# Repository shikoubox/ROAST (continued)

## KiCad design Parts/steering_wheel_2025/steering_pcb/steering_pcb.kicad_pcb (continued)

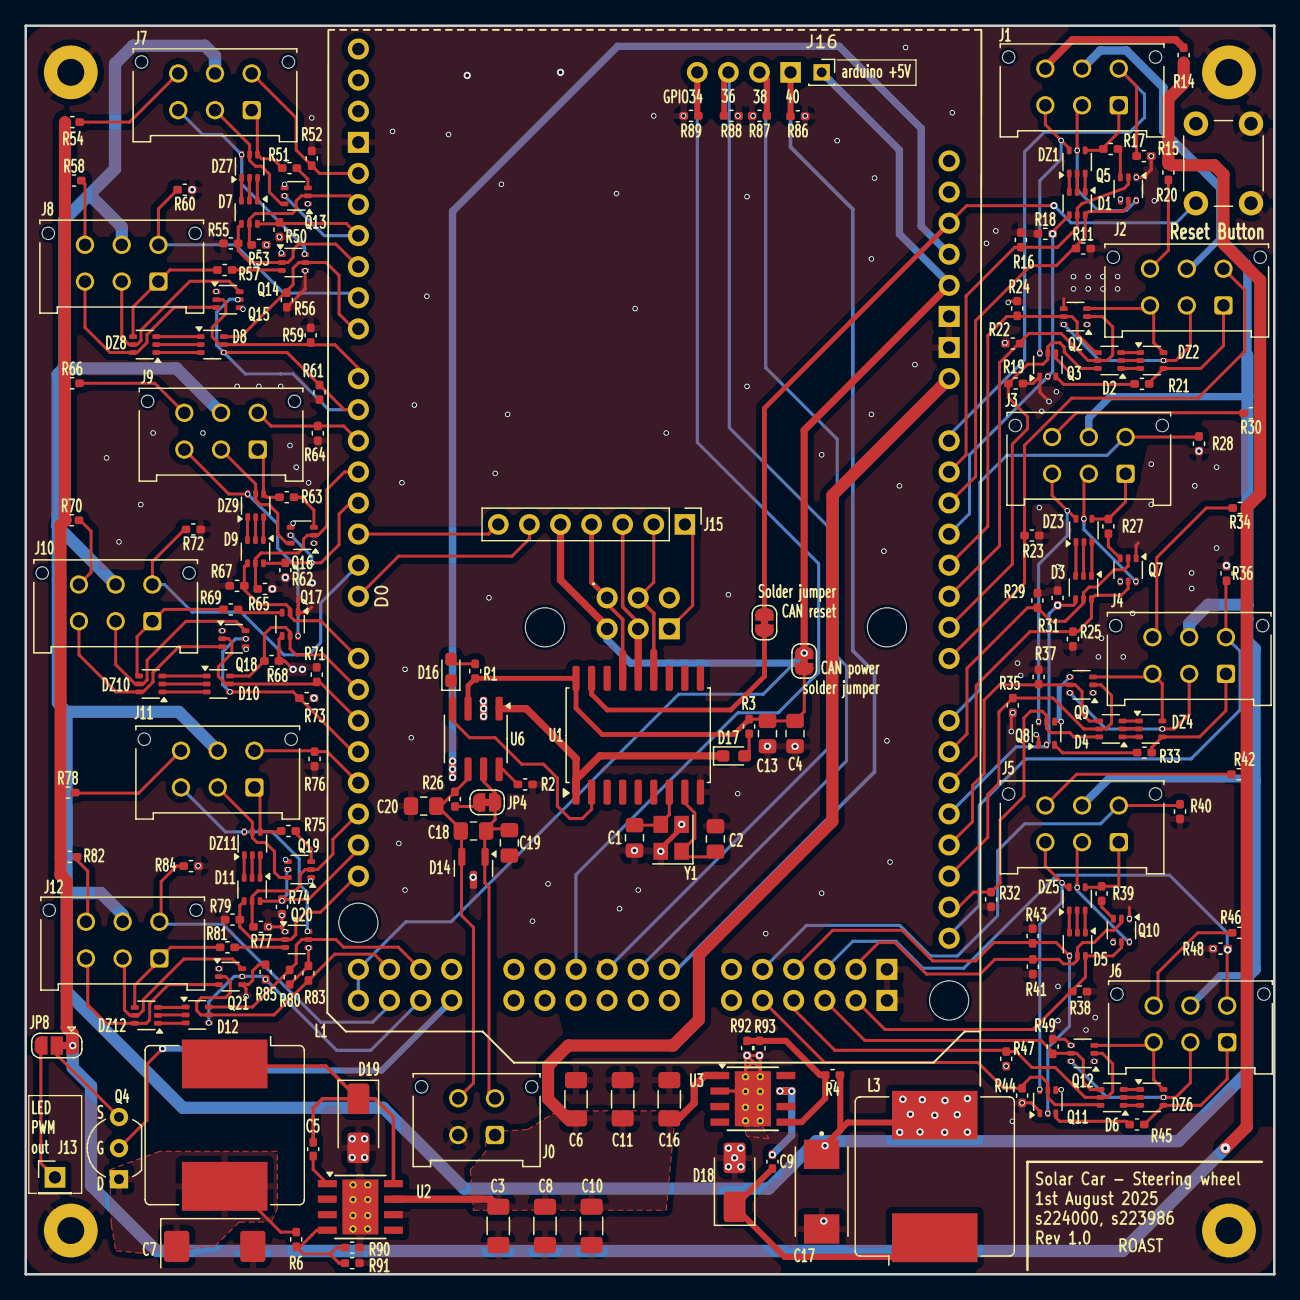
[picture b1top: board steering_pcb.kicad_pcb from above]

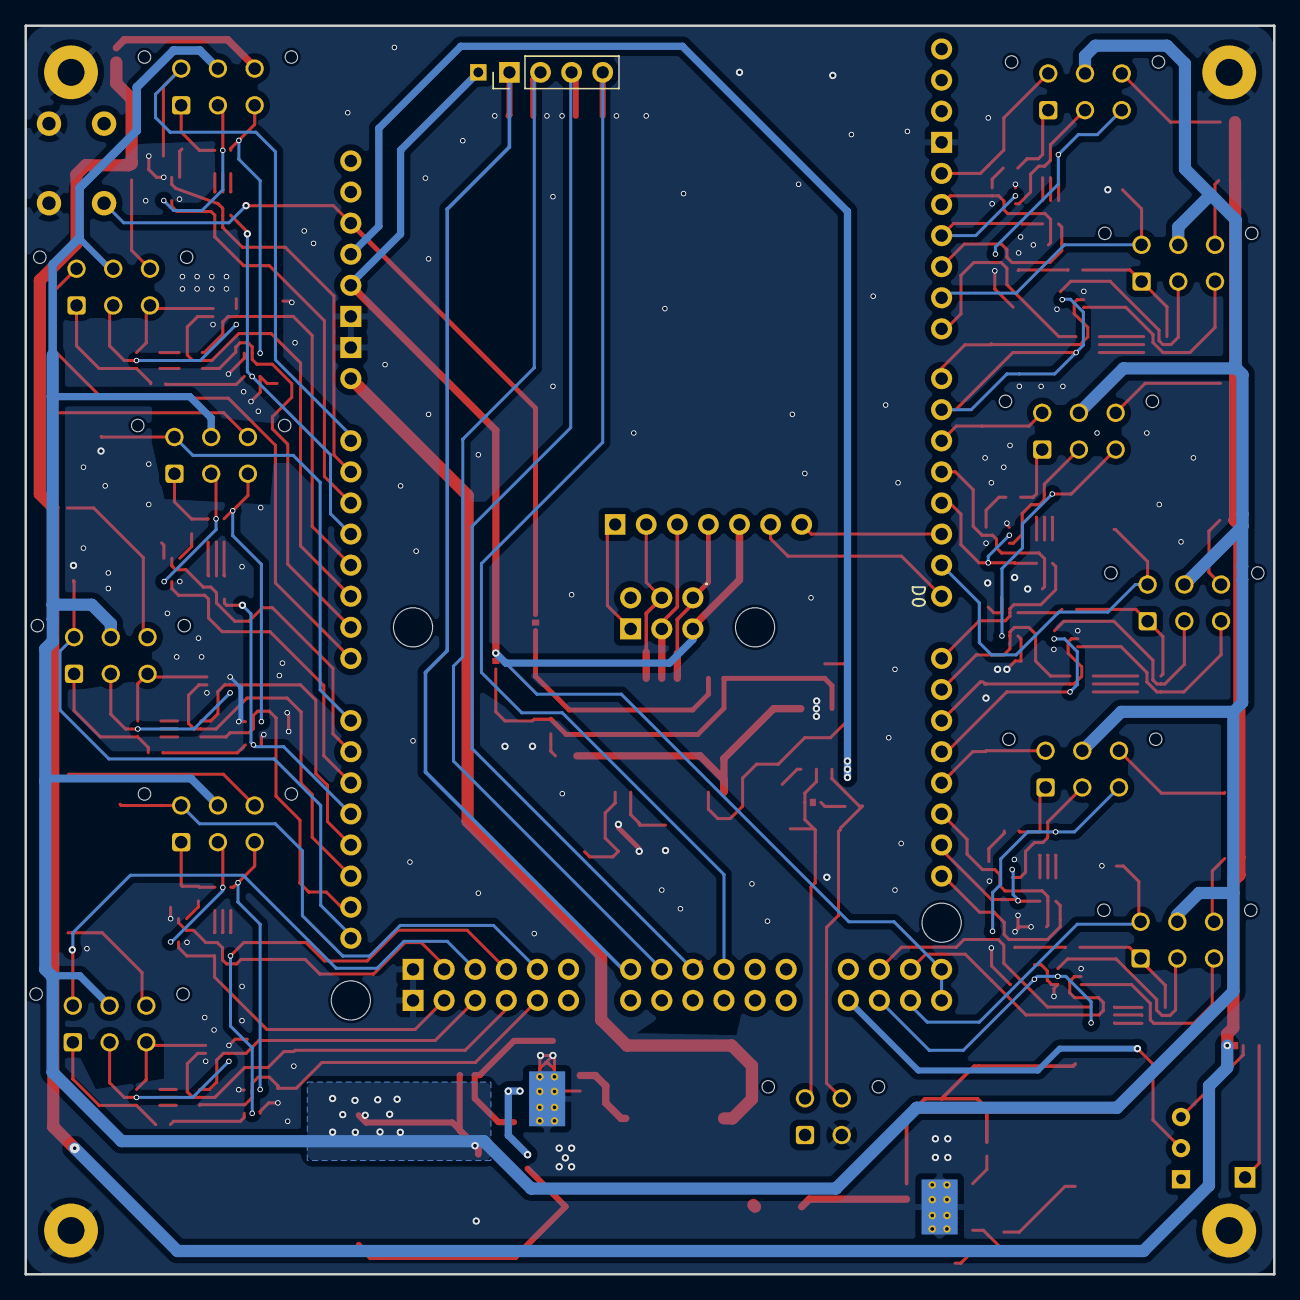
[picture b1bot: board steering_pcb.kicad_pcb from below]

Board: 2 copper layers, 102.0 x 102.0 mm, 185 parts (2 on the bottom side), 183 nets.

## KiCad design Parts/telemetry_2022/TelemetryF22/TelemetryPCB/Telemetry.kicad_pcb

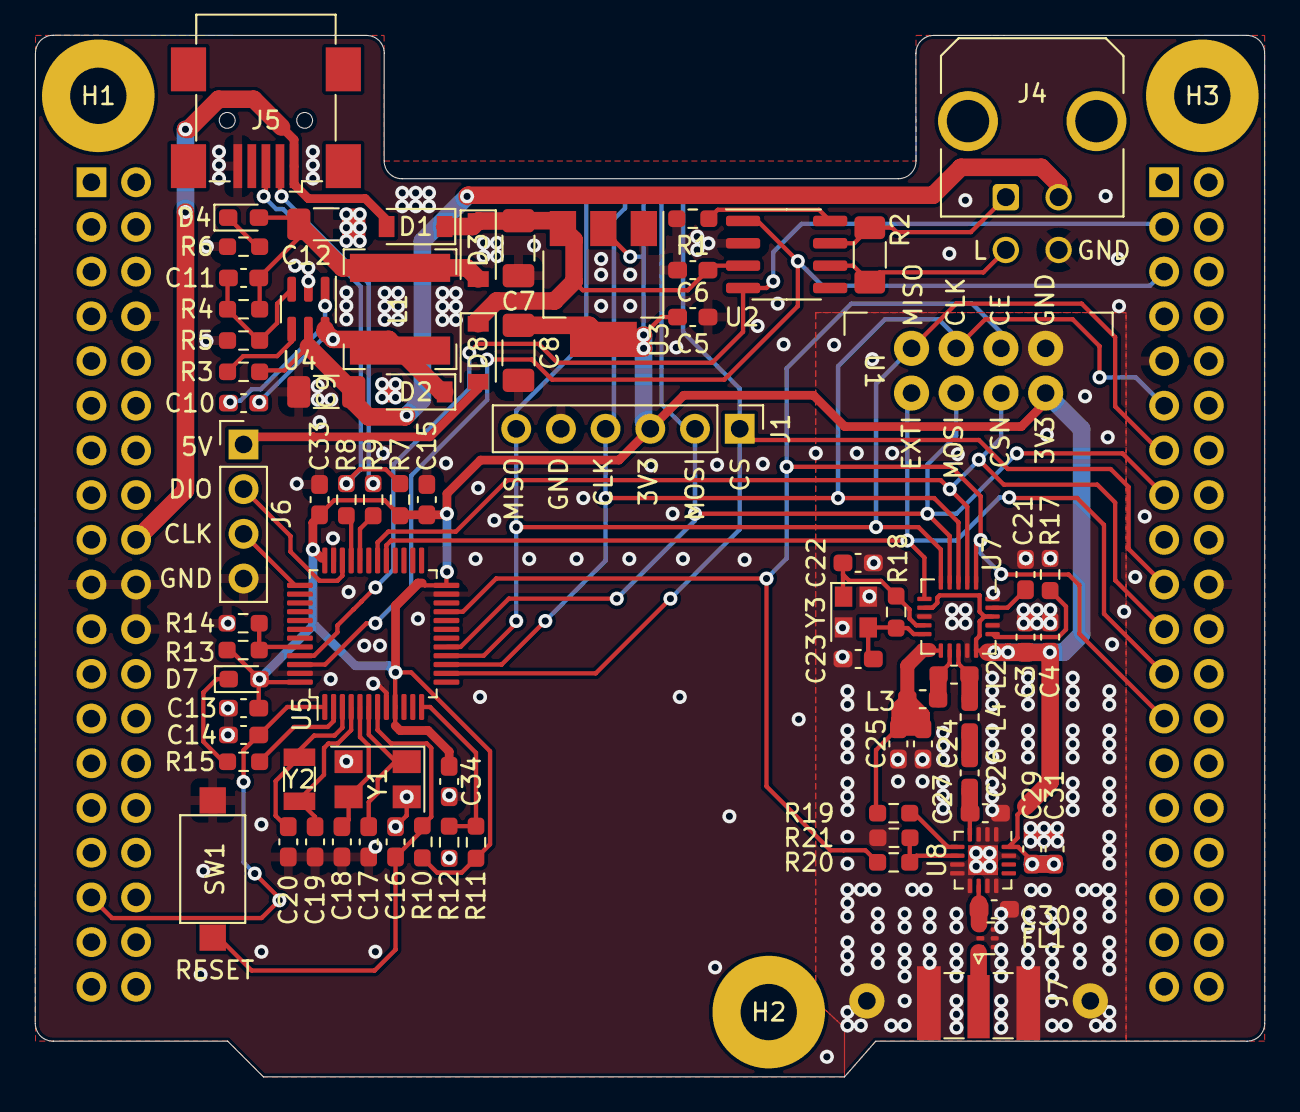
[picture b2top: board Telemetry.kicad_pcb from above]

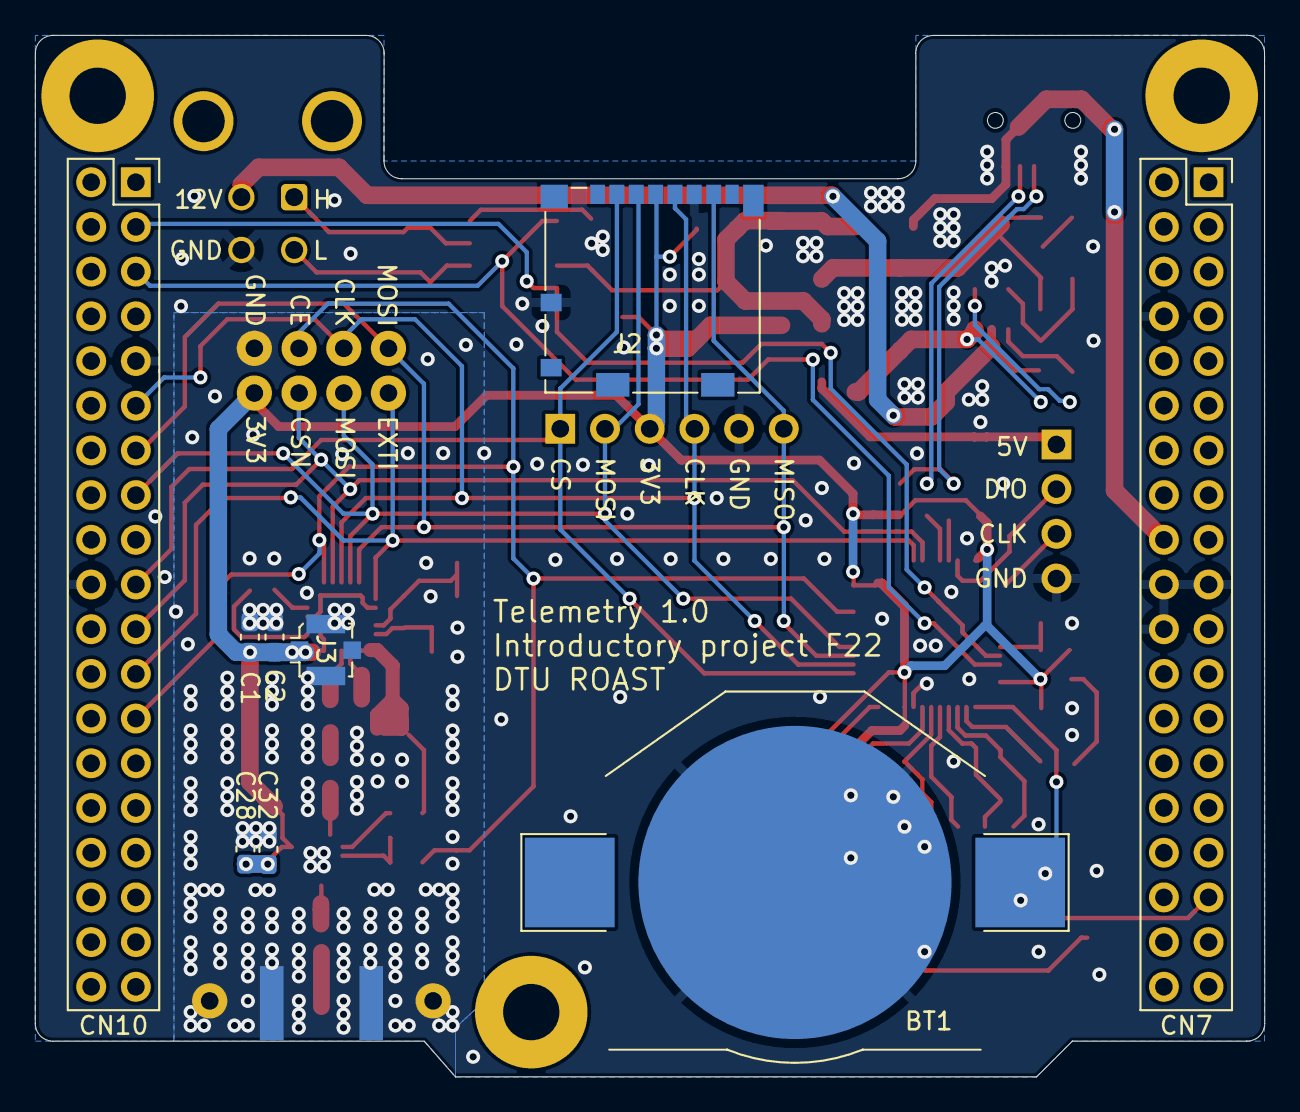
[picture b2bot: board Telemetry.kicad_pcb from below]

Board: 2 copper layers, 69.9 x 59.2 mm, 89 parts (9 on the bottom side), 53 nets.

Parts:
BT1: Battery_Cell; BatteryHolder_Keystone_3002_1x2032
C1, C13, C28: 1u; C_0603_1608Metric_Pad1.08x0.95mm_HandSolder
C2, C32: 100p; C_0603_1608Metric_Pad1.08x0.95mm_HandSolder
C3, C31: 10n; C_0603_1608Metric_Pad1.08x0.95mm_HandSolder
C4, C5, C6, C14, C15, C29, C33, C34: 100n; C_0603_1608Metric_Pad1.08x0.95mm_HandSolder
C7, C8, C9, C12: 10u; C_1206_3216Metric_Pad1.33x1.80mm_HandSolder
C10, C16: 22n; C_0603_1608Metric_Pad1.08x0.95mm_HandSolder
C11: 270p; C_0603_1608Metric_Pad1.08x0.95mm_HandSolder
C17, C18: 33p; C_0603_1608Metric_Pad1.08x0.95mm_HandSolder
C19, C20, C22, C23: 12p; C_0603_1608Metric_Pad1.08x0.95mm_HandSolder
C21: 33n; C_0603_1608Metric_Pad1.08x0.95mm_HandSolder
C24: 2.2n; C_0603_1608Metric_Pad1.08x0.95mm_HandSolder
C25: 4.7p; C_0603_1608Metric_Pad1.08x0.95mm_HandSolder
C26: 1.5p; C_0603_1608Metric_Pad1.08x0.95mm_HandSolder
C27: 1p; C_0603_1608Metric_Pad1.08x0.95mm_HandSolder
C30: 0.3p; C_0603_1608Metric_Pad1.08x0.95mm_HandSolder
CN7, CN10: Conn_02x19_Odd_Even; PinSocket_2x19_P2.54mm_Vertical
D1, D2, D3, D8: PMEG6020AELRX; D_SOD-123
D4, D7: LED_green; LED_0603_1608Metric_Pad1.05x0.95mm_HandSolder
FL1: BFCN-2555; Balun_Johanson_1.6x0.8mm
H1, H2, H3: MountingHole; MountingHole_3.2mm_M3_Pad
J1: Conn_01x06; PinHeader_1x06_P2.54mm_Vertical
J2: Micro_SD_Card; microSD_HC_Molex_104031-0811
J3: Conn_Coaxial; U.FL_Molex_MCRF_73412-0110_Vertical
J4: Conn_02x02_Odd_Even; Molex_Micro-Fit_3.0_43045-0421_2x02-1MP_P3.00mm_Horizontal
J5: USB_B_Mini; USB_Mini-B_Wuerth_65100516121_Horizontal
J6: Conn_01x04; PinHeader_1x04_P2.54mm_Vertical
J7: Conn_Coaxial; SMA_Samtec_SMA-J-P-X-ST-EM1_EdgeMount
L1: 6.8u; L_Bourns-SRN6028
L2: 8.2n; L_0603_1608Metric_Pad1.05x0.95mm_HandSolder
L3: 2.7n; L_0603_1608Metric_Pad1.05x0.95mm_HandSolder
L4: 3.9n; L_0603_1608Metric_Pad1.05x0.95mm_HandSolder
R1: 4.7k; R_0603_1608Metric_Pad0.98x0.95mm_HandSolder
R2: 60; R_1206_3216Metric_Pad1.30x1.75mm_HandSolder
R3: 51k; R_0603_1608Metric_Pad0.98x0.95mm_HandSolder
R4: 39k; R_0603_1608Metric_Pad0.98x0.95mm_HandSolder
R5: 10k; R_0603_1608Metric_Pad0.98x0.95mm_HandSolder
R6, R7, R10, R15: 1.5k; R_0603_1608Metric_Pad0.98x0.95mm_HandSolder
R8, R9: 22R; R_0603_1608Metric_Pad0.98x0.95mm_HandSolder
R11, R12, R13, R14: DNP; R_0603_1608Metric_Pad0.98x0.95mm_HandSolder
R17, R21: 22k; R_0603_1608Metric_Pad0.98x0.95mm_HandSolder
R18: 1M; R_0603_1608Metric_Pad0.98x0.95mm_HandSolder
R19, R20: 1k; R_0603_1608Metric_Pad0.98x0.95mm_HandSolder
SW1: Button; SW_SPST_CK_RS282G05A3
U1: NRF24L01; nRF24L01_LNA
U2: MCP2551-I-P; SOIC-8_3.9x4.9mm_P1.27mm
U3: LM1117-3.3; SOT-223-3_TabPin2
U4: AP5100; SC-74-6_1.5x2.9mm_P0.95mm
U5: STM32F103C6Tx; LQFP-48_7x7mm_P0.5mm
U7: nRF24L01P; QFN-20-1EP_4x4mm_P0.5mm_EP2.5x2.5mm
U8: RFX2401C; QFN-16-1EP_3x3mm_P0.5mm_EP1.7x1.7mm
Y1: Crystal_GND24; Crystal_SMD_5032-4Pin_5.0x3.2mm
Y2: 32 MHz; Crystal_SMD_3215-2Pin_3.2x1.5mm
Y3: 16 MHz; Crystal_SMD_2520-4Pin_2.5x2.0mm

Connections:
/3V3: C1.1, C2.1, C3.1, C4.1, C5.1, C8.1, C13.2, C15.2, C28.1, C29.1, C31.1, C32.1, C33.2, C34.2, D7.2 (A), J1.3, J2.4 (VDD), J3.1 (In), R7.2, R10.1, R11.2, R13.2, U1.2 (VCC), U3.2 (VO), U5.9 (VDDA), U5.24 (VDD), U5.36 (VDD), U5.48 (VDD), U7.7 (VDD), U7.15 (VDD), U7.18 (VDD), U8.16 (VDD)
/5V: C6.1, C7.1, D1.1 (K), D3.1 (K), D8.1 (K), U2.3 (VDD), U3.3 (VI)
/12V: C9.1, J4.2, R3.1, U4.5 (VCC)
/CANH: J4.1, R2.1, U2.7 (CANH)
/CANL: J4.3, R2.2, U2.6 (CANL)
/CAN_RX: CN10.3, U2.4 (RXD), U5.45 (PB8)
/CAN_TX: CN10.5, U2.1 (TXD), U5.46 (PB9)
/CE: CN10.25, R20.2, U1.3 (CE), U5.21 (PB10), U7.1 (CE)
/CLK: CN10.11, J1.4, J2.5 (CLK), U1.5 (SCK), U5.15 (PA5), U7.3 (SCK)
/CS: CN10.19, J1.1, J2.2 (DAT3/CD), U5.14 (PA4)
/CSN: CN10.21, U1.4 (CSN), U5.30 (PA9), U7.2 (CSN)
/EXT5V: C11.1, C12.2, D3.2 (A), D4.2 (A), L1.2, R4.1
/EXTI: CN10.23, U1.8 (IRQ), U5.29 (PA8), U7.6 (IRQ)
/MISO: CN10.13, J1.6, J2.7 (DAT0), U1.7 (MISO), U5.16 (PA6), U7.5 (MISO)
/MOSI: CN10.15, J1.2, J2.3 (CMD), U1.6 (MOSI), U5.17 (PA7), U7.4 (MOSI)
/RXTX: C26.2, C27.2, U8.4 (TXRX)
/STM32F103/BOOT0: R13.1, R14.2, U5.44 (BOOT0)
/STM32F103/NRST: C16.1, R10.2, SW1.2, U5.7 (NRST)
/STM32F103/OSC32IN: C20.1, U5.3 (PC14), Y2.2
/STM32F103/OSC32OUT: C19.2, U5.4 (PC15), Y2.1
/STM32F103/OSCIN: C18.1, U5.5 (PD0), Y1.3
/STM32F103/OSCOUT: C17.2, U5.6 (PD1), Y1.1
/STM32F103/PA2: R11.1, R12.2, U5.12 (PA2)
/STM32F103/PA11: R9.2, U5.32 (PA11)
/STM32F103/PA12: R8.2, U5.33 (PA12)
/STM32F103/PA13: J6.2, U5.34 (PA13)
/STM32F103/PA14: J6.3, U5.37 (PA14)
/STM32F103/PC13: R15.2, U5.2 (PC13)
/SW5V: D8.2 (A), J6.1
/TXEN: C24.2, C25.2, L3.1, R19.2, U7.11 (VDD_PA)
/USB5V: CN7.18, D1.2 (A), J5.1 (VBUS)
/VBAT: BT1.1 (+), C14.1, CN7.33, U5.1 (VBAT)
GND: BT1.2 (-), C1.2, C2.2, C3.2, C4.2, C5.2, C6.2, C7.2, C8.2, C9.2, C12.1, C13.1, C14.2, C15.1, C16.2, C17.1, C18.2, C19.1, C20.2, C21.2, C22.2, C23.2, C24.1, C25.1, C27.1, C28.2, C29.2, C30.1, C31.2, C32.2, C33.1, C34.1, CN7.8, CN7.19, CN7.20, CN7.22, CN10.9, CN10.20, D2.2 (A), FL1.2 (GND), FL1.4 (GND), FL1.5 (GND), FL1.6 (GND), J1.5, J2.6 (VSS), J2.9 (SHIELD), J3.2 (Ext), J4.4, J5.5 (GND), J6.4, J7.2 (Ext), R1.2, R5.2, R6.2, R12.1, R14.1, R17.2, R21.1, SW1.1, U1.1 (GND), U2.2 (VSS), U3.1 (GND), U4.2 (GND), U5.8 (VSSA), U5.23 (VSS), U5.35 (VSS), U5.47 (VSS), U7.8 (VSS), U7.14 (VSS), U7.17 (VSS), U7.20 (VSS), U8.1 (NC), U8.2 (GND), U8.3 (GND), U8.7 (NC), U8.8 (GND), U8.9 (GND), U8.11 (GND), U8.12 (NC), U8.15 (NC), U8.17 (GND), Y1.2, Y1.4, Y3.2, Y3.4
unnamed: C10.1, U4.1 (BST)
unnamed: C10.2, D2.1 (K), L1.1, U4.6 (Lx)
unnamed: C11.2, R4.2, R5.1, U4.3 (FB)
unnamed: C21.1, U7.19 (DVDD)
unnamed: C22.1, R18.1, U7.9 (XC2), Y3.1
unnamed: C23.1, R18.2, U7.10 (XC1), Y3.3
unnamed: C26.1, L4.1
unnamed: C30.2, FL1.1 (IN), U8.10 (ANT)
unnamed: D4.1 (K), R6.1
unnamed: D7.1 (K), R15.1
unnamed: FL1.3 (OUT), J7.1 (In)
unnamed: J5.2 (D-), R9.1
unnamed: J5.3 (D+), R7.1, R8.1
unnamed: L2.1, L3.2, U7.12 (ANT1)
unnamed: L2.2, L4.2, U7.13 (ANT2)
unnamed: R1.1, U2.8 (Rs)
unnamed: R3.2, U4.4 (EN)
unnamed: R17.1, U7.16 (IREF)
unnamed: R19.1, U8.5 (TXEN)
unnamed: R20.1, R21.2, U8.6 (RXEN)

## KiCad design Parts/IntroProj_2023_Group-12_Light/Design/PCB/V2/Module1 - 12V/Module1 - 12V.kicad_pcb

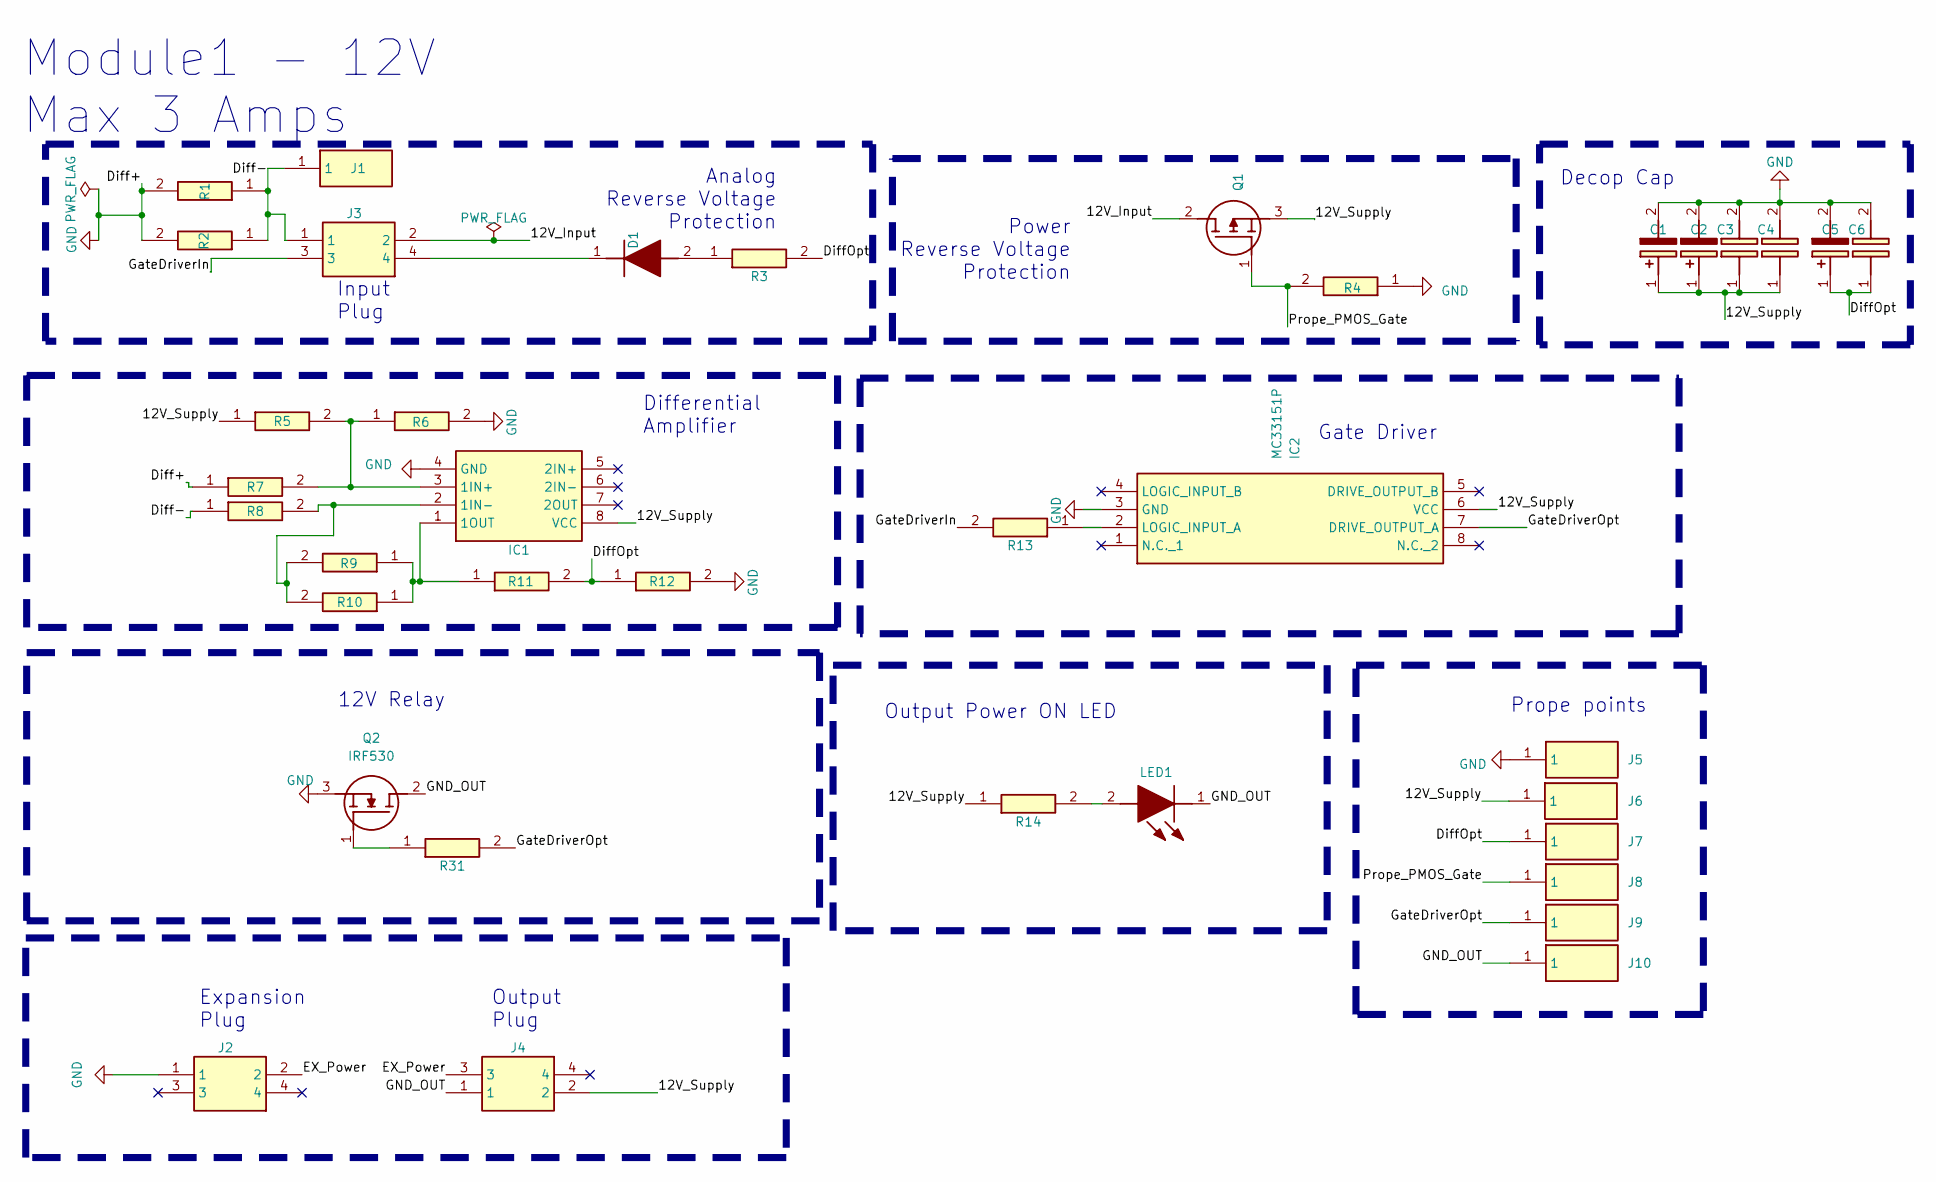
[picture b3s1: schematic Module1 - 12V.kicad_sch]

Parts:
C1, C2, C5: MAL214250102E3; CAPPRD500W60D1300H2200; Manufacturer_Part_Number MAL214250102E3; Mouser Part Number 594-MAL214250102E3
C3, C4, C6: 515D225M100JA6AE3; CAPPRD200W50D500H1100; Manufacturer_Part_Number 515D225M100JA6AE3; Mouser Part Number 75-515D225M100JA6AE3
D1: 1.5KE22CAHE3_A_C; DIOAD2855W107L835D505; Manufacturer_Part_Number 1.5KE22CAHE3_A/C; Mouser Part Number 78-1.5KE22CAHE3_A/C
IC1: LM293P; DIP794W53P254L959H508Q8N; Manufacturer_Part_Number LM293P; Mouser Part Number 595-LM293P
IC2: MC33151P; DIP762W51P254L978H445Q8N; Manufacturer_Part_Number MC33151P
J1, J5, J6, J7, J8, J9, J10: 87224-1; HDRV1W66P0X254_1X1_213X254X1074P; Manufacturer_Part_Number 87224-1; Mouser Part Number 571-872241
J2, J3, J4: 39-30-1040; 39-30-104Y; Manufacturer_Part_Number 39-30-1040; Mouser Part Number 538-39-30-1040
LED1: 228-5045; 2285045; Manufacturer_Part_Number 228-5045
Q1: IRF4905PBF; TO254P469X1042X1967-3P; Manufacturer_Part_Number IRF4905PBF; Mouser Part Number 942-IRF4905PBF
Q2: IRF530; TO255P460X1020X2008-3P; Manufacturer_Part_Number IRF530; Mouser Part Number 511-IRF530
R1, R2: RSAWW51R0; Power Resistor; Manufacturer_Part_Number RSAWW51R0
R3, R13: 1K; Resistor; Manufacturer_Part_Number 293-10K-RC; Mouser Part Number 293-10K-RC
R4, R7, R8: 10K; Resistor; Manufacturer_Part_Number 293-10K-RC; Mouser Part Number 293-10K-RC
R5, R6, R9, R10: 400K; Resistor; Manufacturer_Part_Number 293-10K-RC; Mouser Part Number 293-10K-RC
R11: 100K; Resistor; Manufacturer_Part_Number 293-10K-RC; Mouser Part Number 293-10K-RC
R12: 20K; Resistor; Manufacturer_Part_Number 293-10K-RC; Mouser Part Number 293-10K-RC
R14: 500; Resistor; Manufacturer_Part_Number 293-10K-RC; Mouser Part Number 293-10K-RC
R31: 11K; Resistor; Manufacturer_Part_Number 293-10K-RC; Mouser Part Number 293-10K-RC

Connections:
/12V_Input: J3.2, Q1.2 (D)
/12V_Supply: C1.1 (+), C2.1 (+), C3.1 (+), C4.1 (+), IC1.8 (VCC), IC2.6 (VCC), J4.2, J6.1, Q1.3 (S), R5.1, R14.1
/Diff-: J1.1, J3.1, R1.1, R2.1, R8.1
/DiffOpt: C5.1 (+), C6.1 (+), J7.1, R3.2, R11.2, R12.1
/EX_Power: J2.2, J4.3
/GND_OUT: J4.1, J10.1, LED1.1 (K), Q2.2 (D)
/GateDriverIn: J3.3, R13.2
/GateDriverOpt: IC2.7 (DRIVE_OUTPUT_A), J9.1, R31.2
/Prope_PMOS_Gate: J8.1, Q1.1 (G), R4.2
GND: C1.2 (-), C2.2 (-), C3.2 (-), C4.2 (-), C5.2 (-), C6.2 (-), IC1.4 (GND), IC2.3 (GND), J2.1, J5.1, Q2.3 (S), R1.2, R2.2, R4.1, R6.2, R7.1, R12.2
unnamed: D1.2 (A), R3.1
unnamed: D1.1 (K), J3.4
unnamed: IC1.3 (1IN+), R5.2, R6.1, R7.2
unnamed: IC1.2 (1IN-), R8.2, R9.2, R10.2
unnamed: IC1.1 (1OUT), R9.1, R10.1, R11.1
unnamed: IC2.2 (LOGIC_INPUT_A), R13.1
unnamed: LED1.2 (A), R14.2
unnamed: Q2.1 (G), R31.1

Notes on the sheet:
Output Plug
Expansion Plug
Decop Cap
Differential Amplifier
12V Relay
Prope points
Output Power ON LED
Module1 - 12V Max 3 Amps
Gate Driver
Power Reverse Voltage Protection
Input Plug
Analog Reverse Voltage Protection

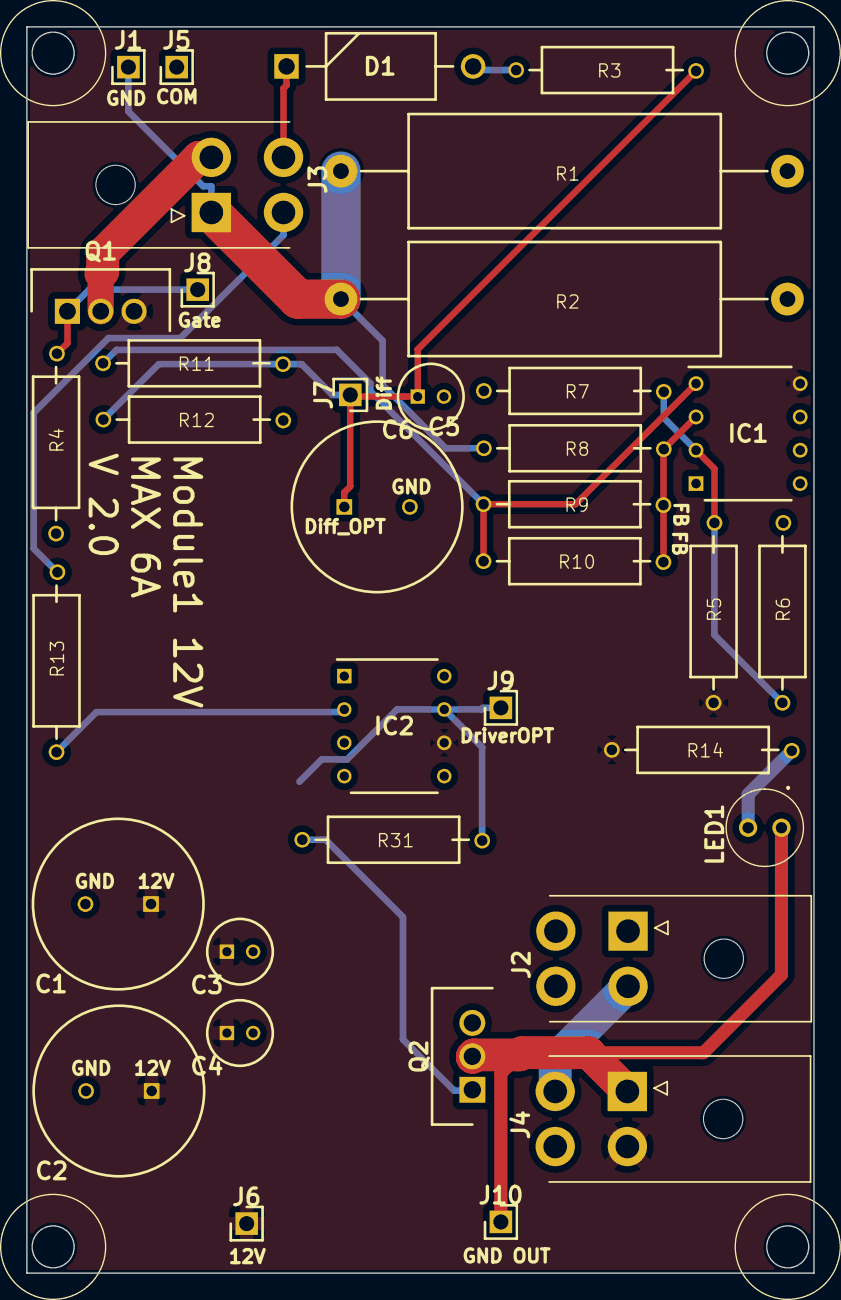
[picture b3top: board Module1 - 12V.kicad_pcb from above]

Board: 2 copper layers, 60.0 x 95.0 mm, 37 parts (0 on the bottom side), 18 nets.

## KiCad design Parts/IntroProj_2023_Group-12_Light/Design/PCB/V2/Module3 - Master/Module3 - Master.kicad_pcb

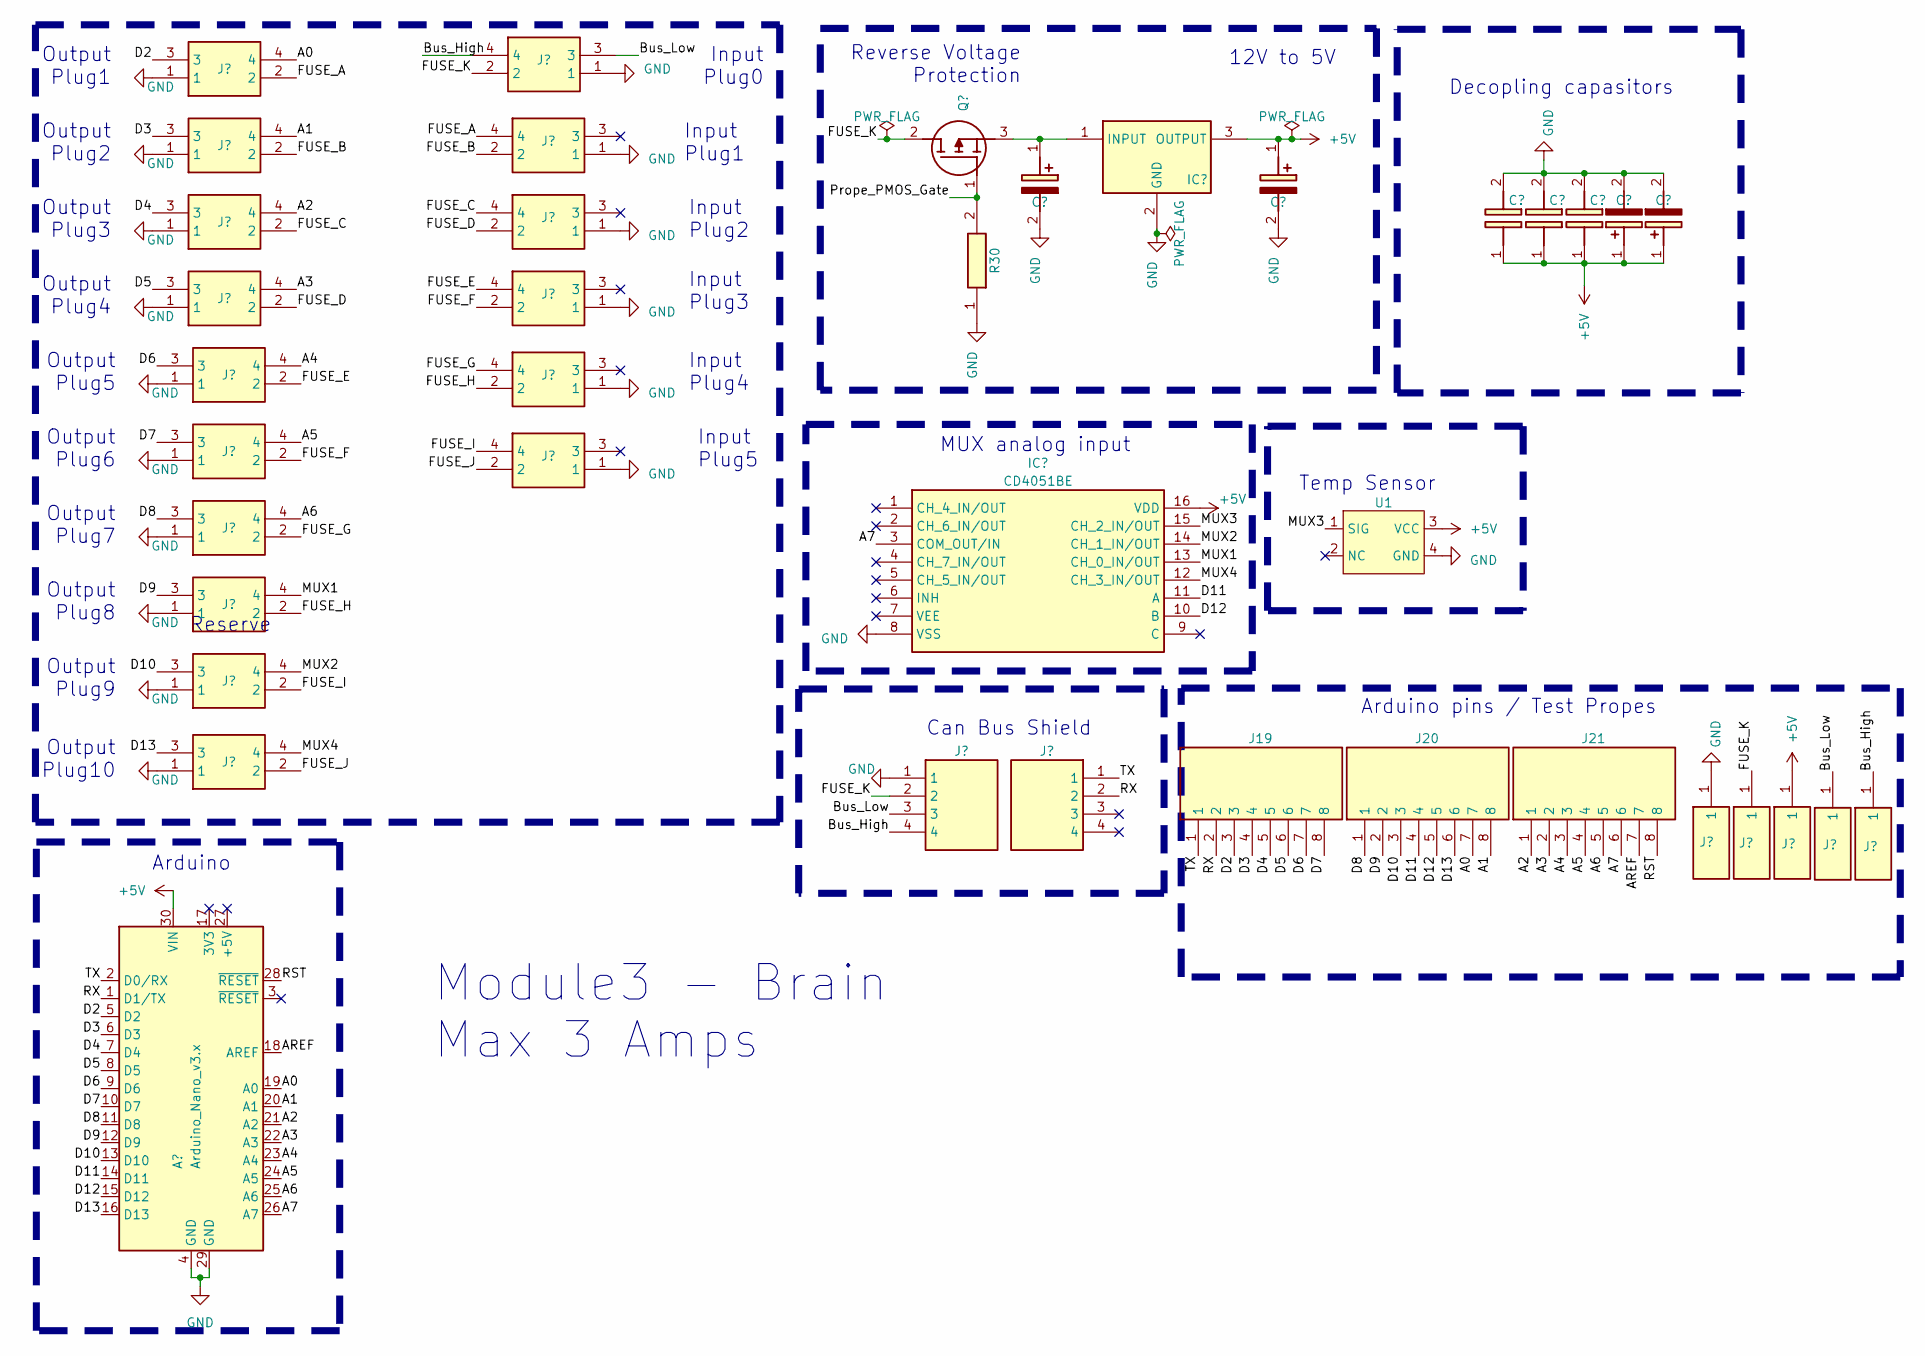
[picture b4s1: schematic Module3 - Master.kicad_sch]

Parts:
A1: Arduino_Nano_v3.x; Arduino_Nano
C1, C2, C6, C7: MAL214250102E3; CAPPRD500W60D1300H2200; Manufacturer_Part_Number MAL214250102E3; Mouser Part Number 594-MAL214250102E3
C3, C4, C5: 515D225M100JA6AE3; CAPPRD200W50D500H1100; Manufacturer_Part_Number 515D225M100JA6AE3; Mouser Part Number 75-515D225M100JA6AE3
IC1: CD4051BE; DIP794W53P254L1930H508Q16N; Manufacturer_Part_Number (descr "A 16-LC-TT"); Mouser Part Number (tags "Connector")
IC2: L7805CV-DG; TO255P460X1020X2008-3P; Manufacturer_Part_Number L7805CV-DG; Mouser Part Number 511-L7805CV-DG
J1, J2, J3, J4, J5, J6, J7, J8, J9, J10: 39-28-1043; Manufacturer_Part_Number 39-28-1043; Mouser Part Number 538-39-28-1043
J11, J12, J13, J14, J15, J16: 39-30-1040; 39-30-104Y; Manufacturer_Part_Number 39-30-1040; Mouser Part Number 538-39-30-1040
J17, J18: 2314876-4; RHDR4W60P0X200_1X4_800X500X450P; Manufacturer_Part_Number 2314876-4; Mouser Part Number 571-2314876-4
J19, J20, J21: SSW-108-02-G-S-RA-001; SHDR8W79P0X254_1X8_2083X241X851P; Manufacturer_Part_Number SSW-108-02-G-S-RA-001
J22, J23, J24, J25, J26: 87224-1; HDRV1W66P0X254_1X1_213X254X1074P; Manufacturer_Part_Number 87224-1; Mouser Part Number 571-872241
Q1: IRF4905PBF; TO254P469X1042X1967-3P; Manufacturer_Part_Number IRF4905PBF; Mouser Part Number 942-IRF4905PBF
R30: 293-10K-RC; Resistor; Manufacturer_Part_Number 293-10K-RC; Mouser Part Number 293-10K-RC
U1: SKU_101020015

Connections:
+5V: A1.30 (VIN), C2.1 (+), C3.1 (+), C4.1 (+), C5.1 (+), C6.1 (+), C7.1 (+), IC1.16 (VDD), IC2.3 (OUTPUT), J24.1, U1.3 (VCC)
/A0: A1.19 (A0), J1.4, J20.7
/A1: A1.20 (A1), J2.4, J20.8
/A2: A1.21 (A2), J3.4, J21.1
/A3: A1.22 (A3), J4.4, J21.2
/A4: A1.23 (A4), J5.4, J21.3
/A5: A1.24 (A5), J6.4, J21.4
/A6: A1.25 (A6), J7.4, J21.5
/A7: A1.26 (A7), IC1.3 (COM_OUT/IN), J21.6
/AREF: A1.18 (AREF), J21.7
/Bus_High: J11.4, J17.4, J26.1
/Bus_Low: J11.3, J17.3, J25.1
/D2: A1.5 (D2), J1.3, J19.3
/D3: A1.6 (D3), J2.3, J19.4
/D4: A1.7 (D4), J3.3, J19.5
/D5: A1.8 (D5), J4.3, J19.6
/D6: A1.9 (D6), J5.3, J19.7
/D7: A1.10 (D7), J6.3, J19.8
/D8: A1.11 (D8), J7.3, J20.1
/D9: A1.12 (D9), J8.3, J20.2
/D10: A1.13 (D10), J9.3, J20.3
/D11: A1.14 (D11), IC1.11 (A), J20.4
/D12: A1.15 (D12), IC1.10 (B), J20.5
/D13: A1.16 (D13), J10.3, J20.6
/FUSE_A: J1.2, J12.4
/FUSE_B: J2.2, J12.2
/FUSE_C: J3.2, J13.4
/FUSE_D: J4.2, J13.2
/FUSE_E: J5.2, J14.4
/FUSE_F: J6.2, J14.2
/FUSE_G: J7.2, J15.4
/FUSE_H: J8.2, J15.2
/FUSE_I: J9.2, J16.4
/FUSE_J: J10.2, J16.2
/FUSE_K: J11.2, J17.2, J23.1, Q1.2 (D)
/MUX1: IC1.13 (CH_0_IN/OUT), J8.4
/MUX2: IC1.14 (CH_1_IN/OUT), J9.4
/MUX3: IC1.15 (CH_2_IN/OUT), U1.1 (SIG)
/MUX4: IC1.12 (CH_3_IN/OUT), J10.4
/Prope_PMOS_Gate: Q1.1 (G); also elsewhere on the board
/RST: A1.28 (~RESET), J21.8
/RX: A1.1 (D1/TX), J18.2, J19.2
/TX: A1.2 (D0/RX), J18.1, J19.1
GND: A1.4 (GND), A1.29 (GND), C1.2 (-), C2.2 (-), C3.2 (-), C4.2 (-), C5.2 (-), C6.2 (-), C7.2 (-), IC1.8 (VSS), IC2.2 (GND), J1.1, J2.1, J3.1, J4.1, J5.1, J6.1, J7.1, J8.1, J9.1, J10.1, J11.1, J12.1, J13.1, J14.1, J15.1, J16.1, J17.1, J22.1, U1.4 (GND); also elsewhere on the board
unnamed: C1.1 (+), IC2.1 (INPUT), Q1.3 (S)

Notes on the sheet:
Output Plug5
Output Plug9
Input Plug0
Output Plug8
Arduino
Input Plug5
Output Plug10
Arduino pins / Test Propes
Output Plug1
Module3 - Brain Max 3 Amps
Temp Sensor
Reserve
Output Plug7
Output Plug4
Reverse Voltage Protection
Output Plug6
Output Plug2
Input Plug2
Input Plug3
12V to 5V
Can Bus Shield
Output Plug3
MUX analog input
Decopling capasitors
Input Plug1
Input Plug4

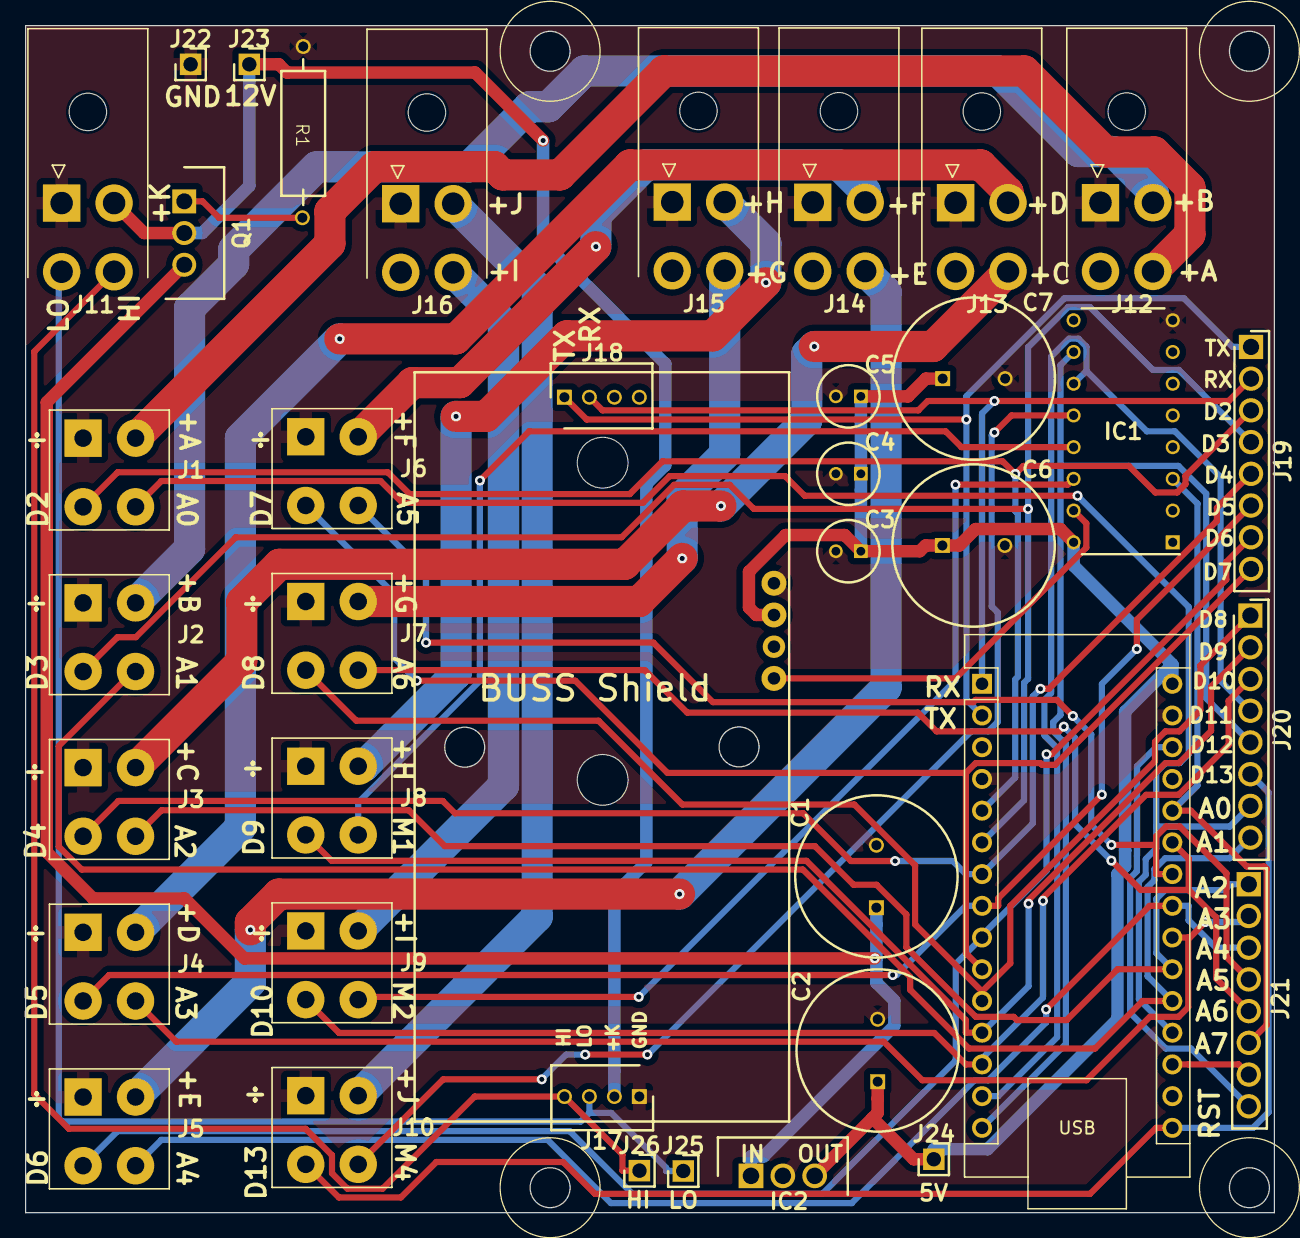
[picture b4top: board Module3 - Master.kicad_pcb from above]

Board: 2 copper layers, 100.0 x 95.1 mm, 39 parts (1 on the bottom side), 45 nets.

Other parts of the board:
R1: 293-10K-RC; Resistor

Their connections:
/Prope_PMOS_Gate: R1.2; also elsewhere on the board
GND: R1.1; also elsewhere on the board
